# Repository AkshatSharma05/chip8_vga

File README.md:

# CHIP-8 on an FPGA 

This project is a CHIP-8 interpreter written in Verilog for the **DE0-Nano** (Cyclone IV). It runs CHIP-8 ROMs directly on the FPGA, displays them over VGA, and accepts input from a PS/2 keyboard.

> This is a work in progress. Some instructions, games, or hardware features may not behave perfectly yet.

---

### Demo Video

---

## What's here

- CHIP-8 CPU and 4 KB memory
- 64×32 framebuffer rendered over VGA
- PS/2 keyboard input
- Buzzer output driven by the CHIP-8 sound timer
- Configurable instruction speed

The default CPU rate is 2,000 instructions per second. Besides improving the
speed of instruction-heavy games, this shortens the interval between the XOR
erase and redraw operations used to move sprites, reducing visible flicker.

## Getting started

Convert a `.ch8` ROM into the memory file used by the design:

```sh
python3 tools/rom_to_hex.py path/to/game.ch8
```

Then open `top.qpf` in Quartus Prime, compile the design, and program the DE0-Nano.

## Keypad

The CHIP-8 keypad is mapped to the left side of a PS/2 keyboard:

```text
Keyboard        CHIP-8
1 2 3 4         1 2 3 C
Q W E R         4 5 6 D
A S D F         7 8 9 E
Z X C V         A 0 B F
```

Either pushbutton resets the system. The status LED blinks while the design is running.

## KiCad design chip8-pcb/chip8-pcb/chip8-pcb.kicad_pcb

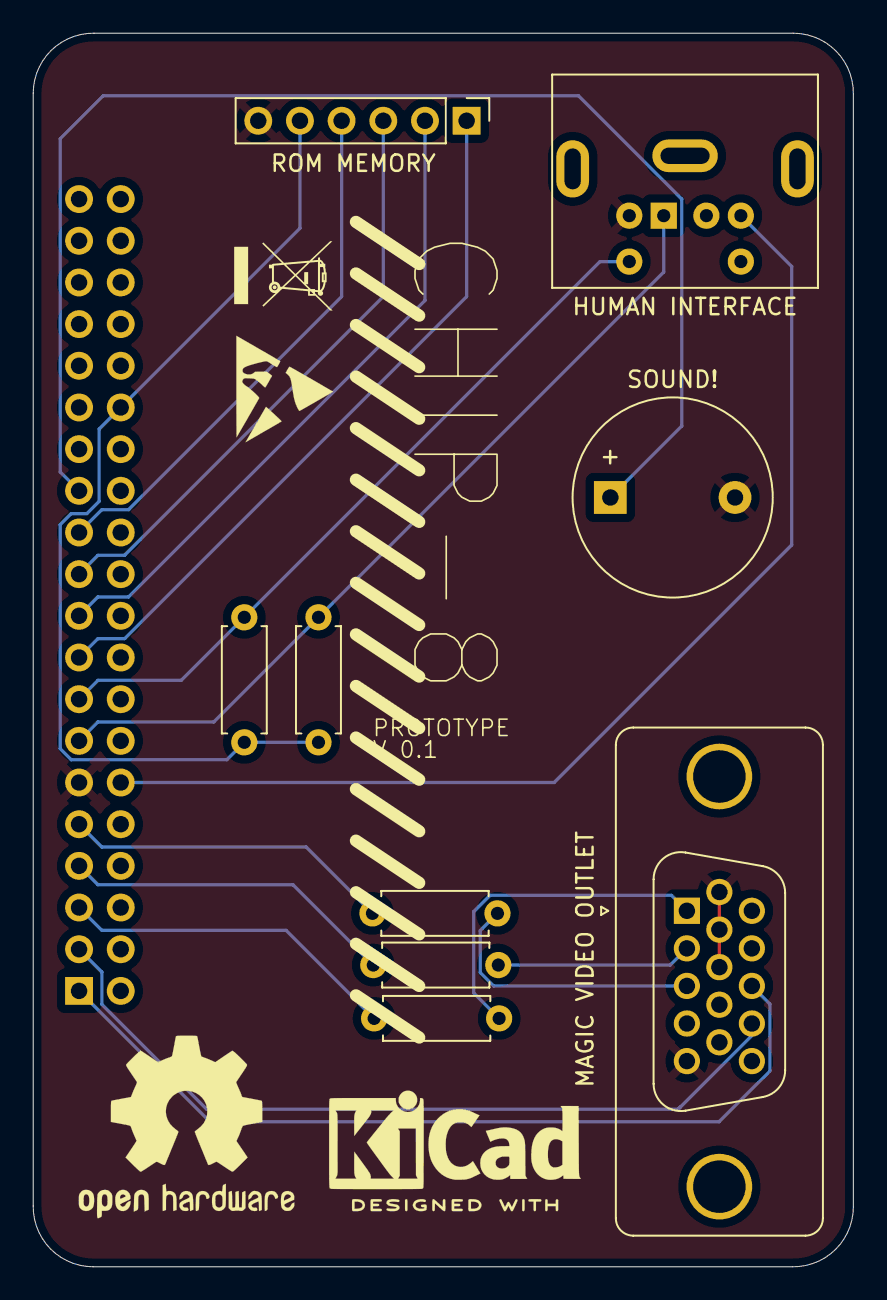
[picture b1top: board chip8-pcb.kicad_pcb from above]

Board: 2 copper layers, 50.0 x 75.2 mm, 10 parts (1 on the bottom side), 18 nets.

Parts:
HUMAN INTERFACE: Mini-DIN-6; Connector_Mini-DIN_Female_6Pin_2rows
J5: Conn_02x20_Odd_Even; PinHeader_2x20_P2.54mm_Vertical
MAGIC VIDEO OUTLET: DE15_Socket_HighDensity; DSUB-15-HD_Socket_Vertical_P2.29x1.98mm_MountingHoles
R1, R2, R3: 270; R_Axial_DIN0207_L6.3mm_D2.5mm_P7.62mm_Horizontal
R4, R5: R; R_Axial_DIN0207_L6.3mm_D2.5mm_P7.62mm_Horizontal
ROM MEMORY: Conn_01x06_Socket; PinHeader_1x06_P2.54mm_Vertical
SOUND!: Buzzer; Buzzer_12x9.5RM7.6

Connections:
3V3: J5.30, R4.1, R5.1, ROM MEMORY.5
B: J5.9, R3.1
BUZ: J5.25, SOUND!.1 (+)
CLK_PS2: HUMAN INTERFACE.5, J5.15, R5.2
CS: J5.17, ROM MEMORY.1
DATA_PS2: HUMAN INTERFACE.1, J5.13, R4.2
G: J5.7, R2.1
GND: HUMAN INTERFACE.3, J5.11, MAGIC VIDEO OUTLET.5, MAGIC VIDEO OUTLET.6, MAGIC VIDEO OUTLET.7, MAGIC VIDEO OUTLET.8, ROM MEMORY.6, SOUND!.2 (-)
HSYNC: J5.3, MAGIC VIDEO OUTLET.14
MISO: J5.23, ROM MEMORY.4
MOSI: J5.21, ROM MEMORY.3
unnamed: MAGIC VIDEO OUTLET.1, R1.2
unnamed: MAGIC VIDEO OUTLET.2, R2.2
unnamed: MAGIC VIDEO OUTLET.3, R3.2
R: J5.5, R1.1
SCK: J5.19, ROM MEMORY.2
VCC_PS2: HUMAN INTERFACE.4, J5.12
VSYNC: J5.1, MAGIC VIDEO OUTLET.13
